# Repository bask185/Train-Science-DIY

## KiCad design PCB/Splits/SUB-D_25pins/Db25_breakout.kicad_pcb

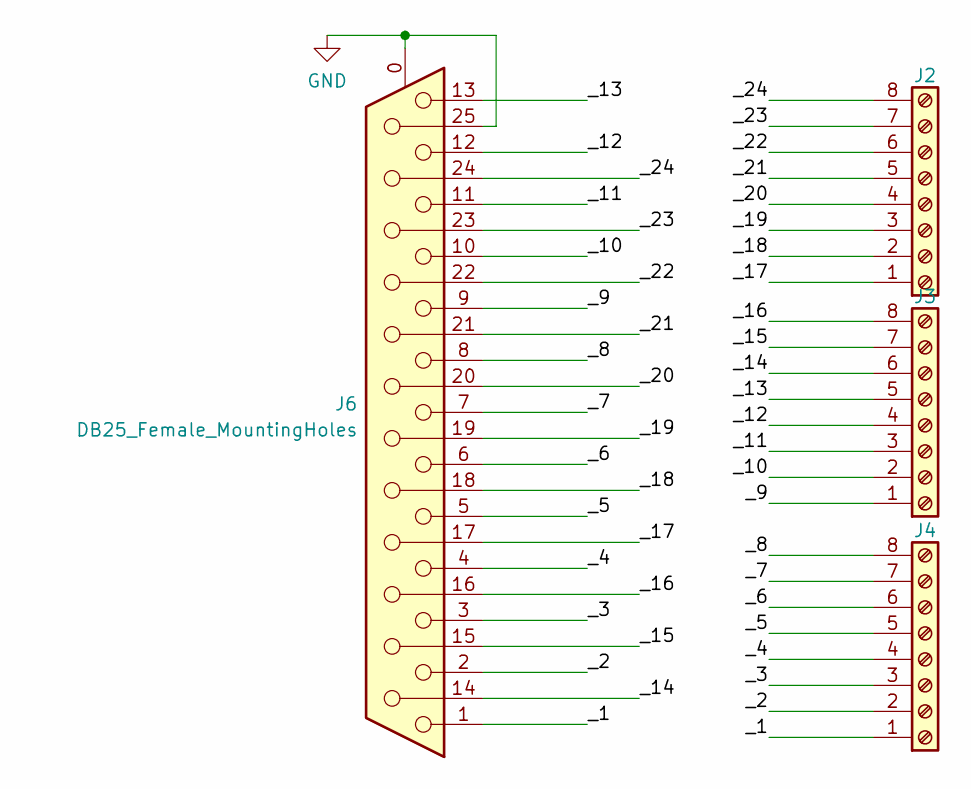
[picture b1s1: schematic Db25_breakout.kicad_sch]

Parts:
J2, J3, J4: Screw_Terminal_01x08; TerminalBlock_Phoenix_MPT-0,5-8-2.54_1x08_P2.54mm_Horizontal
J6: DB25_Female_MountingHoles; DSUB-25_Female_Horizontal_P2.77x2.84mm_EdgePinOffset7.70mm_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

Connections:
/_1: J4.1, J6.1
/_2: J4.2, J6.2
/_3: J4.3, J6.3
/_4: J4.4, J6.4
/_5: J4.5, J6.5
/_6: J4.6, J6.6
/_7: J4.7, J6.7
/_8: J4.8, J6.8
/_9: J3.1, J6.9
/_10: J3.2, J6.10
/_11: J3.3, J6.11
/_12: J3.4, J6.12
/_13: J3.5, J6.13
/_14: J3.6, J6.14
/_15: J3.7, J6.15
/_16: J3.8, J6.16
/_17: J2.1, J6.17
/_18: J2.2, J6.18
/_19: J2.3, J6.19
/_20: J2.4, J6.20
/_21: J2.5, J6.21
/_22: J2.6, J6.22
/_23: J2.7, J6.23
/_24: J2.8, J6.24
GND: J6.0 (PAD), J6.25

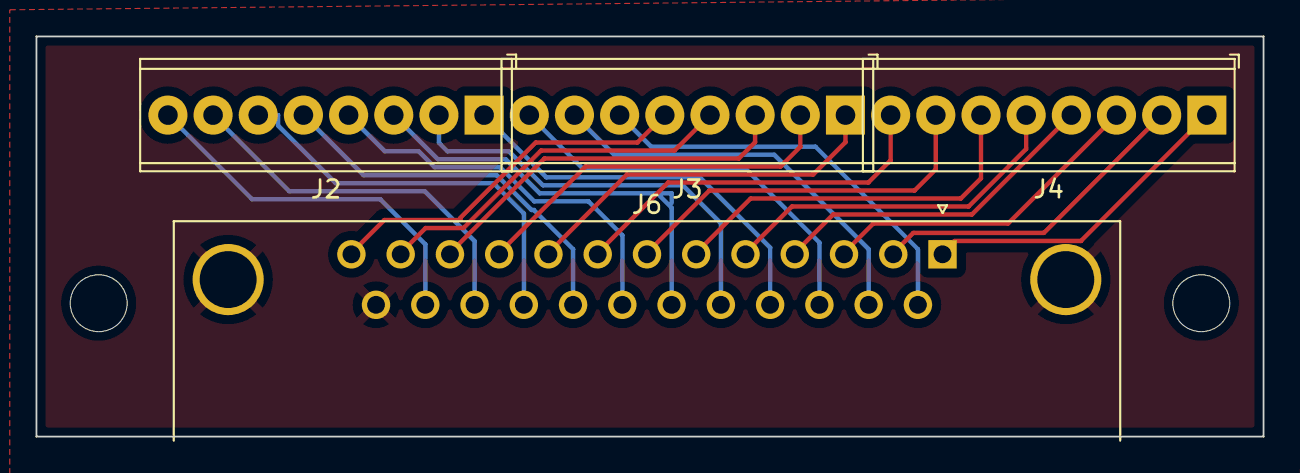
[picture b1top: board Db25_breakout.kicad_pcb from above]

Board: 2 copper layers, 69.0 x 22.5 mm, 4 parts (0 on the bottom side), 25 nets.

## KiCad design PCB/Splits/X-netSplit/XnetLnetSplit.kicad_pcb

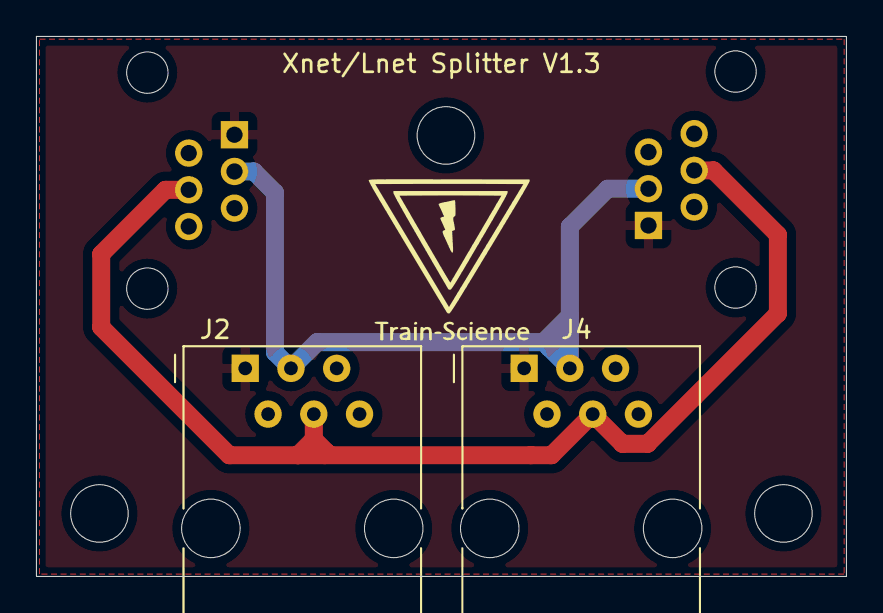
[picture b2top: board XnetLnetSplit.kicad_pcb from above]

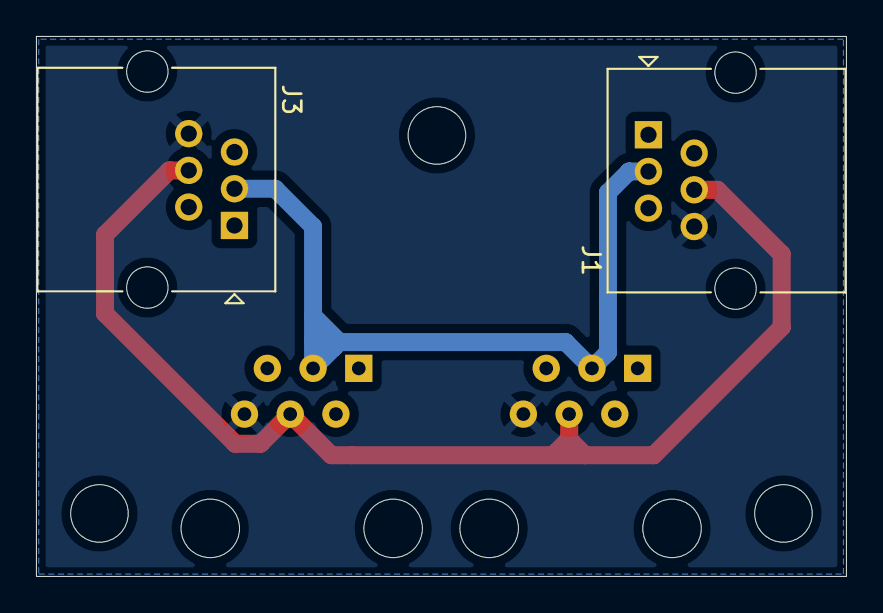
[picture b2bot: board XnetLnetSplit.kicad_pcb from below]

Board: 4 copper layers, 45.0 x 30.0 mm, 4 parts (2 on the bottom side), 6 nets.

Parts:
J1, J3: RJ12; RJ25_Wayconn_MJEA-660X1_Horizontal
J2, J4: RJ12; RJ12_Amphenol_54601

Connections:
unnamed: J1.1, J2.1, J3.1, J4.1
unnamed: J1.2, J2.2, J3.2, J4.2
unnamed: J1.3, J2.3, J3.3, J4.3
unnamed: J1.4, J2.4, J3.4, J4.4
unnamed: J1.5, J2.5, J3.5, J4.5
unnamed: J1.6, J2.6, J3.6, J4.6

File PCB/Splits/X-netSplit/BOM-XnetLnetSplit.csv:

Comment,Designator,Footprint,LCSC
RJ12,J4,RJ12_Amphenol_54601,
RJ12,J2,RJ12_Amphenol_54601,
RJ12,J3,RJ25_Wayconn_MJEA-660X1_Horizontal,
RJ12,J1,RJ25_Wayconn_MJEA-660X1_Horizontal,

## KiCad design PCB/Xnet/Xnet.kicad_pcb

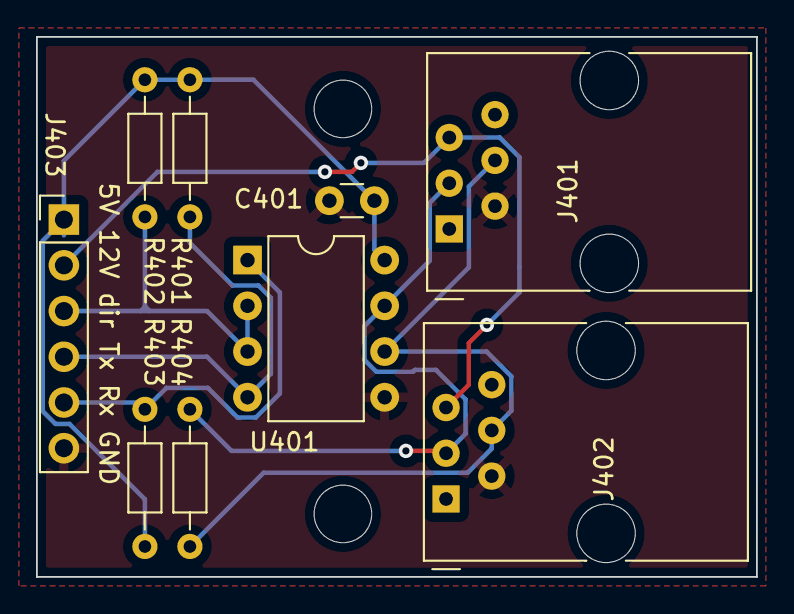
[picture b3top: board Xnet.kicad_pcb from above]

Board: 2 copper layers, 40.0 x 30.0 mm, 9 parts (0 on the bottom side), 8 nets.

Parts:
C401: 100n; C_Disc_D3.0mm_W1.6mm_P2.50mm
J401, J402: RJ12; RJ12_Amphenol_54601
J403: Conn_01x06_Male; PinHeader_1x06_P2.54mm_Vertical
R401, R402, R403: 10k; R_Axial_DIN0204_L3.6mm_D1.6mm_P7.62mm_Horizontal
R404: 120R; R_Axial_DIN0204_L3.6mm_D1.6mm_P7.62mm_Horizontal
U401: MAX485E; DIP-8_W7.62mm

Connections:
+5V: C401.1, J403.1, R401.2, R402.2, R403.2, U401.8 (VCC)
+12V: J401.5, J402.5, J403.2
/Xnet/A: J401.4, J402.4, R404.1, U401.6 (A)
/Xnet/B: J401.3, J402.3, R404.2, U401.7 (B)
GND: C401.2, J401.2, J402.2, J403.6, U401.5 (GND)
Rx: J403.5, R403.1, U401.1 (RO)
Tx: J403.4, R401.1, U401.4 (DI)
dir: J403.3, R402.1, U401.2 (~RE), U401.3 (DE)

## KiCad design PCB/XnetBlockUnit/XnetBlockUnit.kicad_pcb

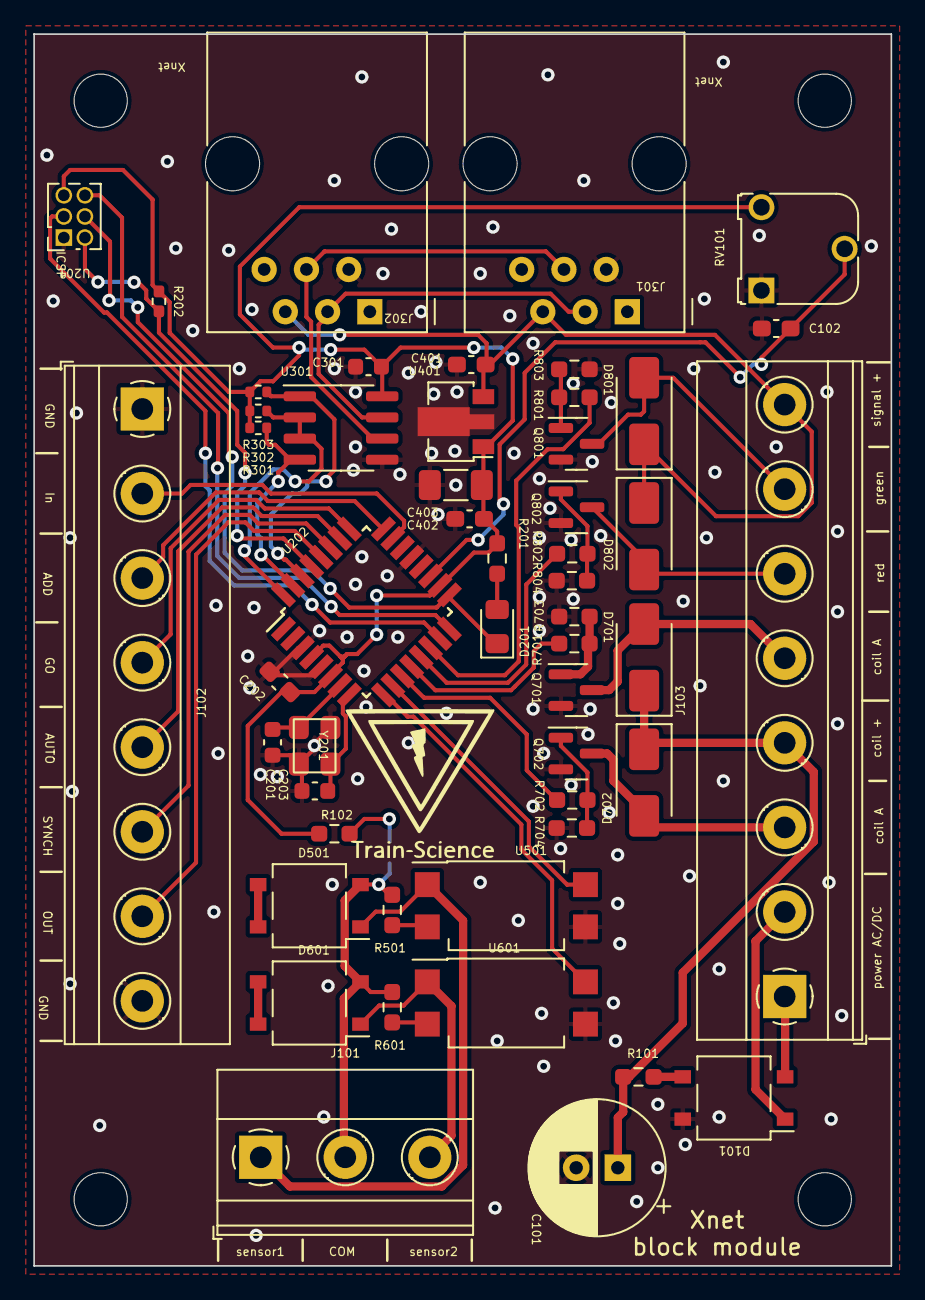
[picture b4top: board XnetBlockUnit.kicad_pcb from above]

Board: 2 copper layers, 51.5 x 74.0 mm, 52 parts (1 on the bottom side), 48 nets.

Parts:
C101: 2000uF; CP_Radial_D8.0mm_P2.50mm
C102, C202, C402: 100nF; C_0603_1608Metric_Pad1.08x0.95mm_HandSolder
C201, C203: 12pF; C_0603_1608Metric
C301: 100nF; C_0603_1608Metric
C401: 330nF; C_0603_1608Metric_Pad1.08x0.95mm_HandSolder
C403: 100uF; C_1206_3216Metric_Pad1.33x1.80mm_HandSolder
D101, D501, D601: MB6S; TO-269AA
D201: LED; LED_0805_2012Metric_Pad1.15x1.40mm_HandSolder
D701, D702, D801, D802: D_SMA
J101: sensor; TerminalBlock_Phoenix_MKDS-1,5-3-5.08_1x03_P5.08mm_Horizont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
J102, J103: Screw_Terminal_01x08; TerminalBlock_Phoenix_MKDS-1,5-8-5.08_1x08_P5.08mm_Horizont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
J301, J302: RJ12
JP101: SolderJumper_2_Open; SolderJumper-2_P1.3mm_Open_RoundedPad1.0x1.5mm
Q701, Q702, Q801, Q802: SOT-23
R101: 100R; R_0603_smalltext
R102: 1k; R_0603_smalltext
R201: 6k2; R_0603_1608Metric_Pad0.98x0.95mm_HandSolder
R202: 10k; R_0402_1005Metric_Pad0.72x0.64mm_HandSolder
R301, R302, R303: 10k; R_0402_1005Metric
R501, R601: 47k; R_0603_smalltext
R701, R702, R703, R704, R801, R802, R803, R804: R_0603_1608Metric_Pad0.98x0.95mm_HandSolder
RV101: R_Potentiometer; Potentiometer_Runtron_RM-065_Vertical
U201: HEADER_3x2; PinSocket_2x03_P1.27mm_Vertical
U202: ATmega328-A; TQFP-32_7x7mm_P0.8mm
U301: MAX485E; SOIC-8_3.9x4.9mm_P1.27mm
U401: L78L05_SOT89; SOT-89-3
U501, U601: EL814; SSO-4_6.7x5.1mm_P2.54mm_Clearance8mm
Y201: Crystal_GND2; crystal_arduino

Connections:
+5V: C202.2, C301.1, C402.1, C403.1, R102.1, R201.1, R202.1, R301.1, R302.1, R303.1, RV101.3, U201.5, U202.4 (VCC), U202.6 (VCC), U202.18 (AVCC), U301.8 (VCC), U401.1 (OUT)
+12V: C401.1, D801.1 (K), D802.1 (K), J103.8, J301.5, J302.5, U401.3 (IN)
/AC1: D101.1, J103.2
/AC2: D101.2, J103.1
/In: J102.2, U202.23 (PC0)
/Out: J102.7, U202.28 (PC5)
/Xnet/A: J301.4, J302.4, U301.6 (A)
/Xnet/B: J301.3, J302.3, U301.7 (B)
/Xnet/RS485_DIR: R302.2, U202.32 (PD2), U301.2 (~RE), U301.3 (DE)
/Xnet/Rx: R303.2, U202.30 (PD0), U301.1 (RO)
/Xnet/Tx: R301.2, U202.31 (PD1), U301.4 (DI)
/add: J102.3, U202.24 (PC1)
/atmega/A6: C102.2, RV101.2, U202.19 (ADC6)
/atmega/LED: D201.1 (K), U201.4, U202.17 (PB5)
/atmega/MISO: U201.6, U202.16 (PB4)
/atmega/MOSI: U201.3, U202.15 (PB3)
/atmega/X1: C201.2, U202.7 (XTAL1/PB6), Y201.1
/atmega/X2: C203.2, U202.8 (XTAL2/PB7), Y201.3
/atmega/reset: R202.2, U201.2, U202.29 (~RESET/PC6)
/auto: J102.5, U202.26 (PC3)
/coil_A: D701.2 (A), J103.5, Q701.3 (D)
/coil_A_TTL: R702.1, U202.11 (PD7)
/coil_B: D702.2 (A), J103.3, Q702.3 (D)
/coil_B_TTL: R701.1, U202.12 (PB0)
/coil_pow: C101.1, D701.1 (K), D702.1 (K), J103.4, R101.1
/go: J102.4, U202.25 (PC2)
/green: D801.2 (A), J103.7, Q801.3 (D)
/red: D802.2 (A), J103.6, Q802.3 (D)
/sens_1: U202.10 (PD6), U501.4
/sens_2: U202.9 (PD5), U601.4
/sensor1/COM: D501.2, D601.2, J101.2, JP101.1 (A), R501.2, R601.2
/sensor1/TRACK: D501.1, J101.1, U501.1
/sensor2/TRACK: D601.1, J101.3, U601.1
/signal_R: R801.1, U202.14 (PB2)
/signal_g: R802.1, U202.13 (PB1)
/synch: J102.6, U202.27 (PC4)
GND: C101.2, C102.1, C201.1, C202.1, C203.1, C301.2, C401.2, C402.2, C403.2, D101.4 (-), J102.1, J102.8, J301.2, J302.2, Q701.2 (S), Q702.2 (S), Q801.2 (S), Q802.2 (S), R703.1, R704.1, R803.1, R804.1, RV101.1, U201.1, U202.3 (GND), U202.5 (GND), U202.21 (GND), U301.5 (GND), U401.2 (GND), U501.3, U601.3, Y201.2 (GND), Y201.4 (GND)
unnamed: D101.3 (+), R101.2
unnamed: D201.2 (A), R201.2
unnamed: D501.3 (+), D501.4 (-)
unnamed: D601.3 (+), D601.4 (-)
unnamed: JP101.2 (B), R102.2
unnamed: Q701.1 (G), R701.2, R703.2
unnamed: Q702.1 (G), R702.2, R704.2
unnamed: Q801.1 (G), R801.2, R803.2
unnamed: Q802.1 (G), R802.2, R804.2
unnamed: R501.1, U501.2
unnamed: R601.1, U601.2

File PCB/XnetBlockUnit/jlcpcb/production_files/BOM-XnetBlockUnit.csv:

Comment,Designator,Footprint,LCSC
Crystal_GND2,Y201,crystal_arduino,C13738
100nF,"C202,C301,C402",C_0603_1608Metric_Pad1.08x0.95mm_HandSolder,C14663
ATmega328-A,U202,TQFP-32_7x7mm_P0.8mm,C14877
100uF,C403,C_1206_3216Metric_Pad1.33x1.80mm_HandSolder,C15008
330nF,C401,C_0603_1608Metric_Pad1.08x0.95mm_HandSolder,C1615
~,"Q701,Q702,Q801,Q802",SOT-23,C20917
1k,R102,R_0603_smalltext,C21190
100R,R101,R_0603_smalltext,C22775
~,"R701,R702,R801,R802",R_0603_1608Metric_Pad0.98x0.95mm_HandSolder,C23345
MB6S,"D101,D501,D601",TO-269AA,C2488
10k,"R202,R301,R302,R303",R_0402_1005Metric_Pad0.72x0.64mm_HandSolder,C25744
~,"R703,R704,R803,R804",R_0603_1608Metric_Pad0.98x0.95mm_HandSolder,C25804
47k,"R501,R601",R_0603_smalltext,C25819
12pF,"C201,C203",C_0603_1608Metric,C38523
6k2,R201,R_0603_1608Metric_Pad0.98x0.95mm_HandSolder,C4260
EL814,"U501,U601",SSO-4_6.7x5.1mm_P2.54mm_Clearance8mm,C500388
MAX485E,U301,SOIC-8_3.9x4.9mm_P1.27mm,C668206
L78L05_SOT89,U401,SOT-89-3,C71136
LED,D201,LED_0805_2012Metric_Pad1.15x1.40mm_HandSolder,C84256
~,"D701,D702,D801,D802",D_SMA,C8678
Screw_Terminal_01x08,J103,"TerminalBlock_Phoenix_MKDS-1,5-8-5.08_1x08_P5.08mm_Horizontal",
2000uF,C101,CP_Radial_D8.0mm_P2.50mm,
sensor,J101,"TerminalBlock_Phoenix_MKDS-1,5-3-5.08_1x03_P5.08mm_Horizontal",
HEADER_3x2,U201,PinSocket_2x03_P1.27mm_Vertical,
Screw_Terminal_01x08,J102,"TerminalBlock_Phoenix_MKDS-1,5-8-5.08_1x08_P5.08mm_Horizontal",
RJ12,J302,RJ12,
RJ12,J301,RJ12,
SolderJumper_2_Open,JP101,SolderJumper-2_P1.3mm_Open_RoundedPad1.0x1.5mm,

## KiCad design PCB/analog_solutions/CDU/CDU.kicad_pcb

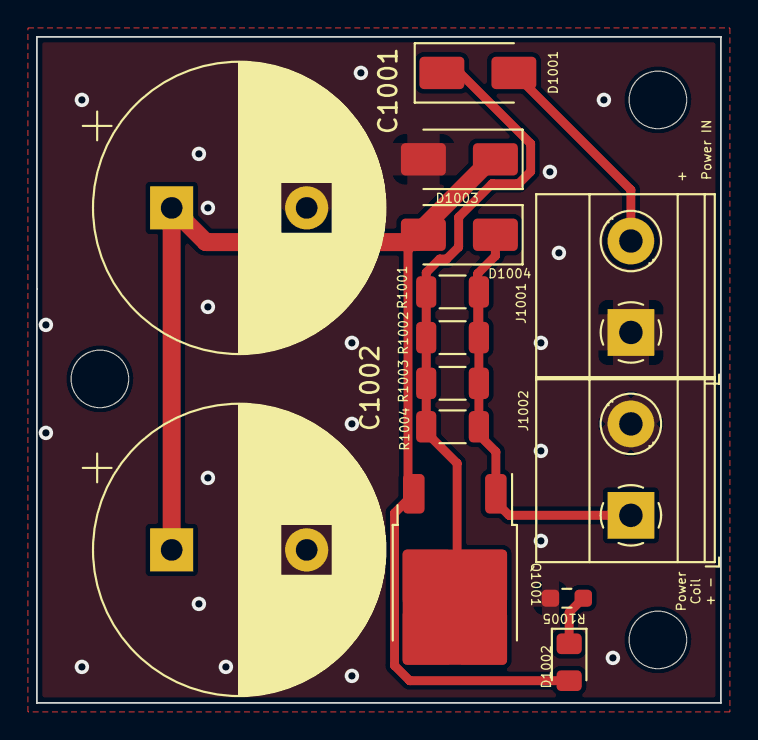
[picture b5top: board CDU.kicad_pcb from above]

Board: 2 copper layers, 38.0 x 37.0 mm, 14 parts (0 on the bottom side), 6 nets.

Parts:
C1001: 1000uF]; CP_Radial_D16.0mm_P7.50mm
C1002: 1000uF; CP_Radial_D16.0mm_P7.50mm
D1001, D1003, D1004: D; D_SMA
D1002: LED; LED_0805_2012Metric_Pad1.15x1.40mm_HandSolder
J1001, J1002: Screw_Terminal_01x02; TerminalBlock_Phoenix_MKDS-1,5-2-5.08_1x02_P5.08mm_Horizont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
Q1001: 4A_DARLINGTON; TO-252-2
R1001, R1002, R1003, R1004: 2k; R_1206_smalltext
R1005: 1k; R_0603_smalltext

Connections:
/AC1(+): D1001.2 (A), J1001.2
/OUT+: D1004.1 (K), J1002.1, Q1001.1 (B), R1001.2, R1002.2, R1003.2, R1004.2
GND: C1001.2, C1002.2, D1003.2 (A), J1001.1, J1002.2, R1005.2
unnamed: D1001.1 (K), Q1001.2 (C), R1001.1, R1002.1, R1003.1, R1004.1
unnamed: C1001.1, C1002.1, D1002.2 (A), D1003.1 (K), D1004.2 (A), Q1001.3 (E)
unnamed: D1002.1 (K), R1005.1

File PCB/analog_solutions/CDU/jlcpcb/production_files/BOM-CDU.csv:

Comment,Designator,Footprint,LCSC
4A_DARLINGTON,Q1001,TO-252-2,C12789
2k,"R1001,R1002,R1003,R1004",R_1206_smalltext,C17944
1k,R1005,R_0603_smalltext,C21190
D,"D1001,D1003,D1004",D_SMA,C22452
LED,D1002,LED_0805_2012Metric_Pad1.15x1.40mm_HandSolder,C2296

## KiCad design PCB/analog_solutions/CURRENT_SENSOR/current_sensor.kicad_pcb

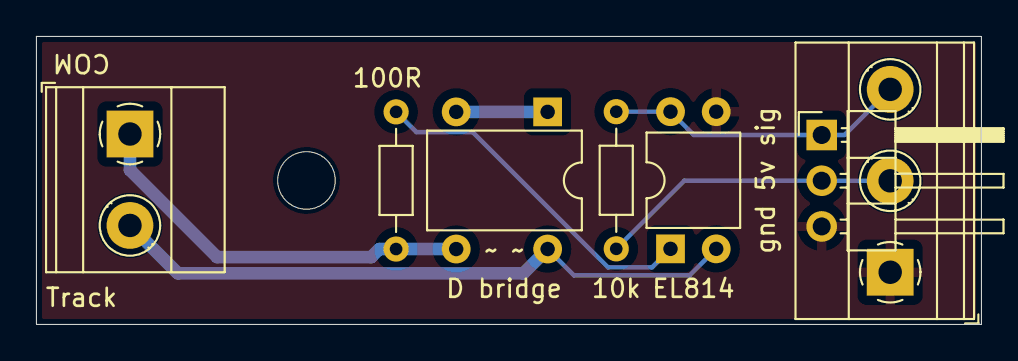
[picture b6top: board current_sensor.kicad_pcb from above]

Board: 2 copper layers, 52.5 x 16.0 mm, 7 parts (0 on the bottom side), 7 nets.

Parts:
D1201: D; Diode_Bridge_DIP-4_W7.62mm_P5.08mm
J1201: tracks; TerminalBlock_Phoenix_MKDS-1,5-2-5.08_1x02_P5.08mm_Horizont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
J1202: ter; TerminalBlock_Phoenix_MKDS-1,5-3-5.08_1x03_P5.08mm_Horizont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
J1203: ter; PinHeader_1x03_P2.54mm_Horizontal
R1201: 100R; R_Axial_DIN0204_L3.6mm_D1.6mm_P7.62mm_Horizontal
R1202: 10k; R_Axial_DIN0204_L3.6mm_D1.6mm_P7.62mm_Horizontal
U1201: EL814; DIP-4_W7.62mm

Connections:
+5V: J1202.2, J1203.2, R1202.1
GND: J1202.1, J1203.3, U1201.3
unnamed: D1201.1 (+), D1201.2 (-)
unnamed: D1201.3, J1201.1, R1201.1
unnamed: D1201.4, J1201.2, U1201.2
unnamed: R1201.2, U1201.1
sig: J1202.3, J1203.1, R1202.2, U1201.4

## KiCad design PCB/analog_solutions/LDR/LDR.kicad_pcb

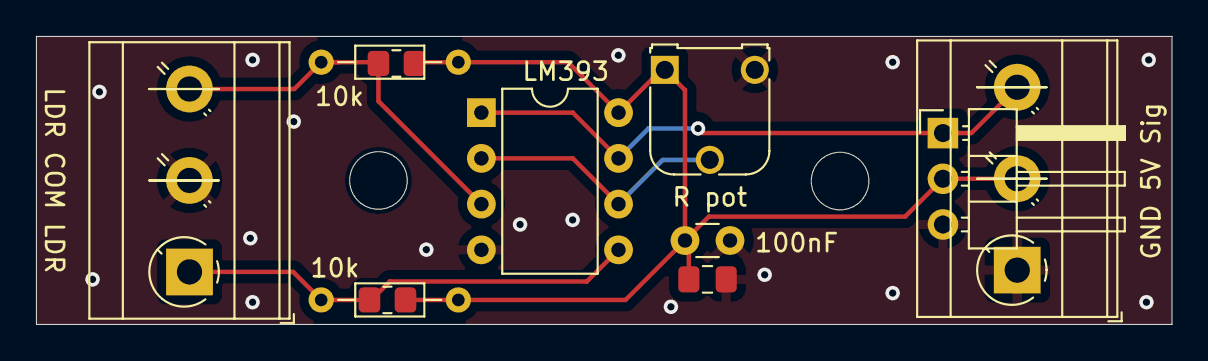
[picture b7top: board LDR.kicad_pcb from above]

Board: 2 copper layers, 63.1 x 16.0 mm, 8 parts (0 on the bottom side), 6 nets.

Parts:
C: 100nF; C_Disc_D3.0mm_W1.6mm_P2.50mm
J1101: LDR; TerminalBlock_MetzConnect_Type073_RT02603HBLU_1x03_P5.08mm_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
J1102: ter; PinHeader_1x03_P2.54mm_Horizontal
J1103: ter; TerminalBlock_MetzConnect_Type073_RT02603HBLU_1x03_P5.08mm_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
R1101, R1102: 10k; R_Axial_DIN0204_L3.6mm_D1.6mm_P7.62mm_Horizontal
R pot: REF; Potentiometer_Runtron_RM-065_Vertical
U1101: LM393; DIP-8_W7.62mm

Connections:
+5V: C.1, J1102.2, J1103.2, R1101.1, R1102.1, R pot.1, U1101.8 (V+)
GND: C.2, J1101.2, J1102.3, J1103.1, R pot.3, U1101.4 (V-)
unnamed: J1101.1, R1101.2, U1101.5 (+)
unnamed: J1101.3, R1102.2, U1101.3 (+)
unnamed: J1102.1, J1103.3, U1101.1, U1101.7
unnamed: R pot.2, U1101.2 (-), U1101.6 (-)

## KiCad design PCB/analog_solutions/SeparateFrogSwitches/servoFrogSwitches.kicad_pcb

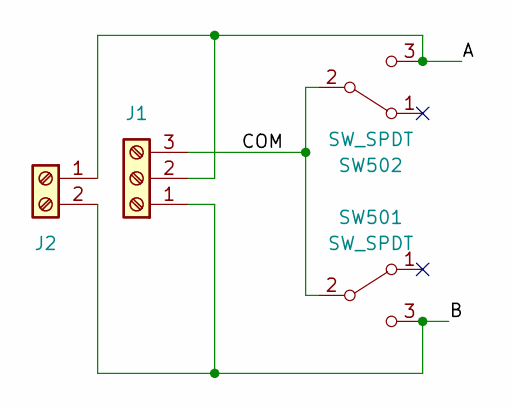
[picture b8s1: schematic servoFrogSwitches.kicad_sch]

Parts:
J1: Screw_Terminal_01x03; PhoenixContact_MC_1,5_3-G-3.5_1x03_P3.50mm_Horizontal
J2: Screw_Terminal_01x02; PhoenixContact_MC_1,5_2-G-3.5_1x02_P3.50mm_Horizontal
SW501, SW502: SW_SPDT; limitSwitch

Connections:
/A: J1.2, J2.1, SW502.3 (C)
/B: J1.1, J2.2, SW501.3 (C)
/COM: J1.3, SW501.2 (B), SW502.2 (B)

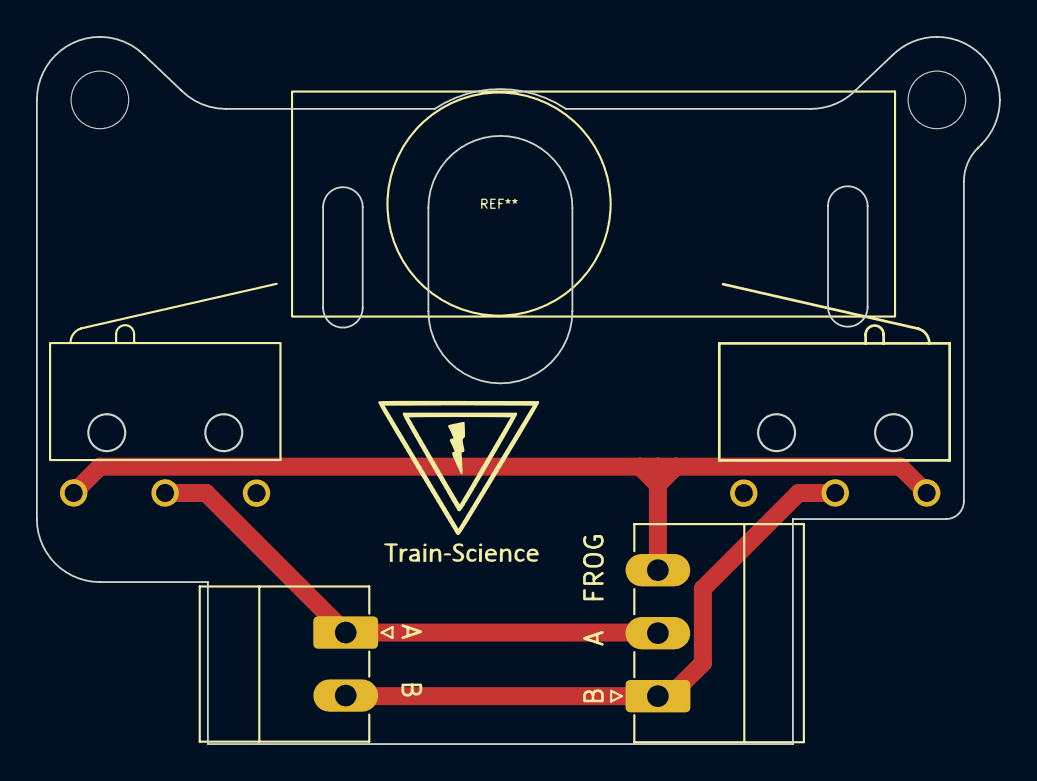
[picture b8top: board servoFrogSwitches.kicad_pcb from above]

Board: 2 copper layers, 53.5 x 39.3 mm, 4 parts (1 on the bottom side), 3 nets.
